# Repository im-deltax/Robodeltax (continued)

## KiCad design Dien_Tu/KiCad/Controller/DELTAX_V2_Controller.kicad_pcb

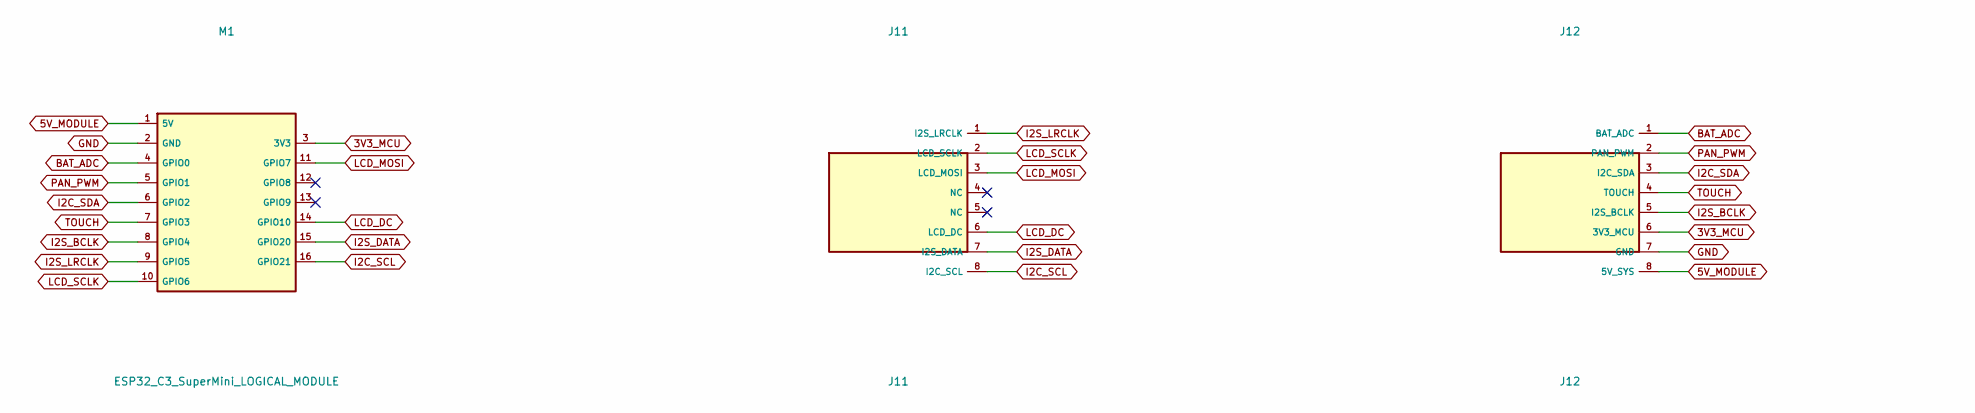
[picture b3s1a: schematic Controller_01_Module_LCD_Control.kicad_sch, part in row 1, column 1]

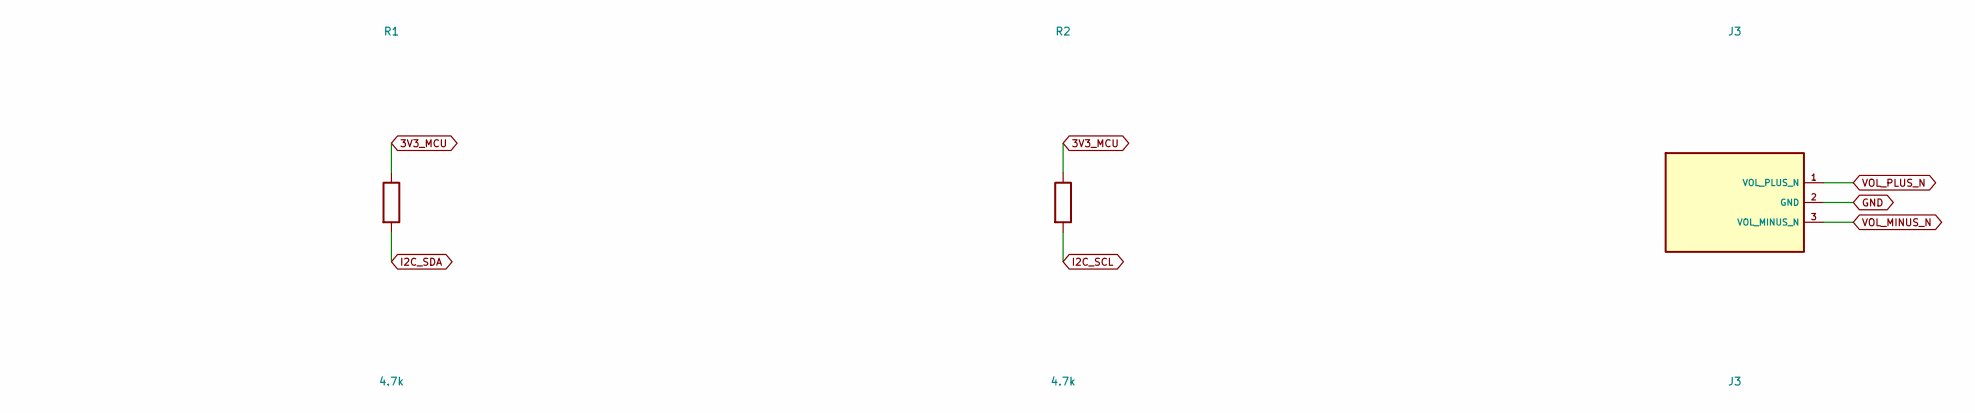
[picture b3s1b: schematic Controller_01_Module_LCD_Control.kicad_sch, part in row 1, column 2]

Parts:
J3: J3; WirePads_3
J11: J11; SLW_108_LowProfile
J12: J12; SLW_108_LowProfile
M1: ESP32_C3_SuperMini_LOGICAL_MODULE
R1, R2: 4.7k; R_0603_1608Metric

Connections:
3V3_MCU: J12.6 (3V3_MCU), M1.3 (3V3), R1.1, R2.1; also elsewhere on the board
5V_MODULE: J12.8 (5V_SYS), M1.1 (5V); also elsewhere on the board
BAT_ADC: J12.1 (BAT_ADC), M1.4 (GPIO0); also elsewhere on the board
GND: J3.2 (GND), J12.7 (GND), M1.2 (GND); also elsewhere on the board
I2C_SCL: J11.8 (I2C_SCL), M1.16 (GPIO21), R2.2; also elsewhere on the board
I2C_SDA: J12.3 (I2C_SDA), M1.6 (GPIO2), R1.2; also elsewhere on the board
I2S_BCLK: J12.5 (I2S_BCLK), M1.8 (GPIO4); also elsewhere on the board
I2S_DATA: J11.7 (I2S_DATA), M1.15 (GPIO20); also elsewhere on the board
I2S_LRCLK: J11.1 (I2S_LRCLK), M1.9 (GPIO5); also elsewhere on the board
LCD_DC: J11.6 (LCD_DC), M1.14 (GPIO10); also elsewhere on the board
LCD_MOSI: J11.3 (LCD_MOSI), M1.11 (GPIO7); also elsewhere on the board
LCD_SCLK: J11.2 (LCD_SCLK), M1.10 (GPIO6); also elsewhere on the board
PAN_PWM: J12.2 (PAN_PWM), M1.5 (GPIO1); also elsewhere on the board
TOUCH: J12.4 (TOUCH), M1.7 (GPIO3); also elsewhere on the board
VOL_MINUS_N: J3.3 (VOL_MINUS_N); also elsewhere on the board
VOL_PLUS_N: J3.1 (VOL_PLUS_N); also elsewhere on the board

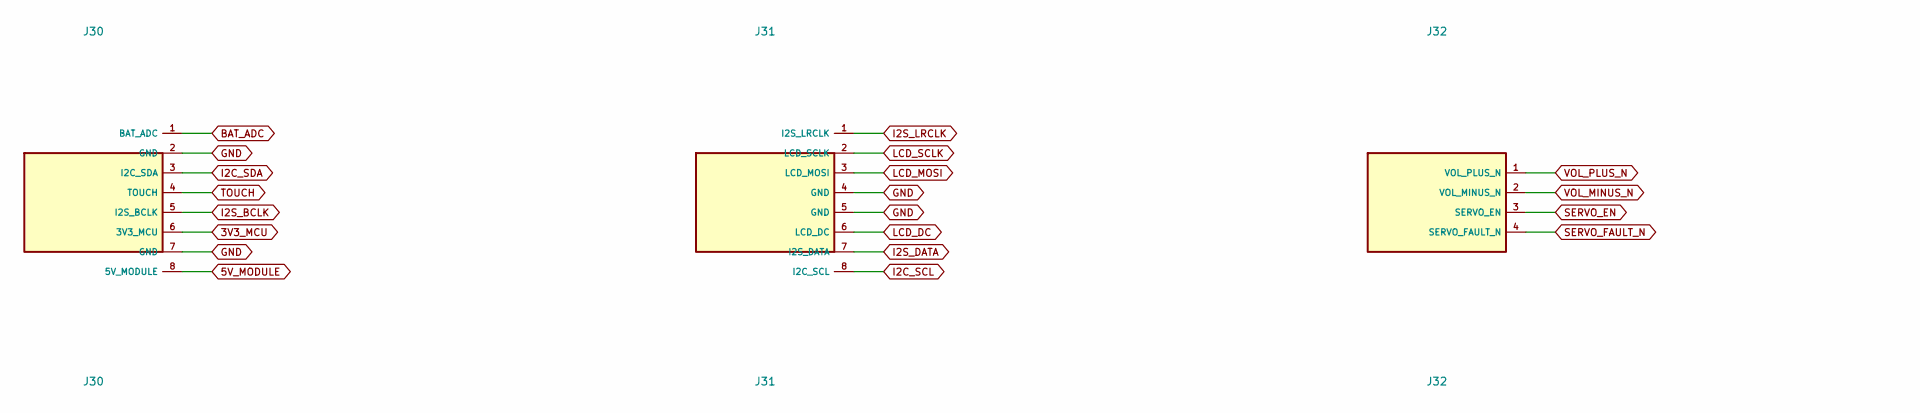
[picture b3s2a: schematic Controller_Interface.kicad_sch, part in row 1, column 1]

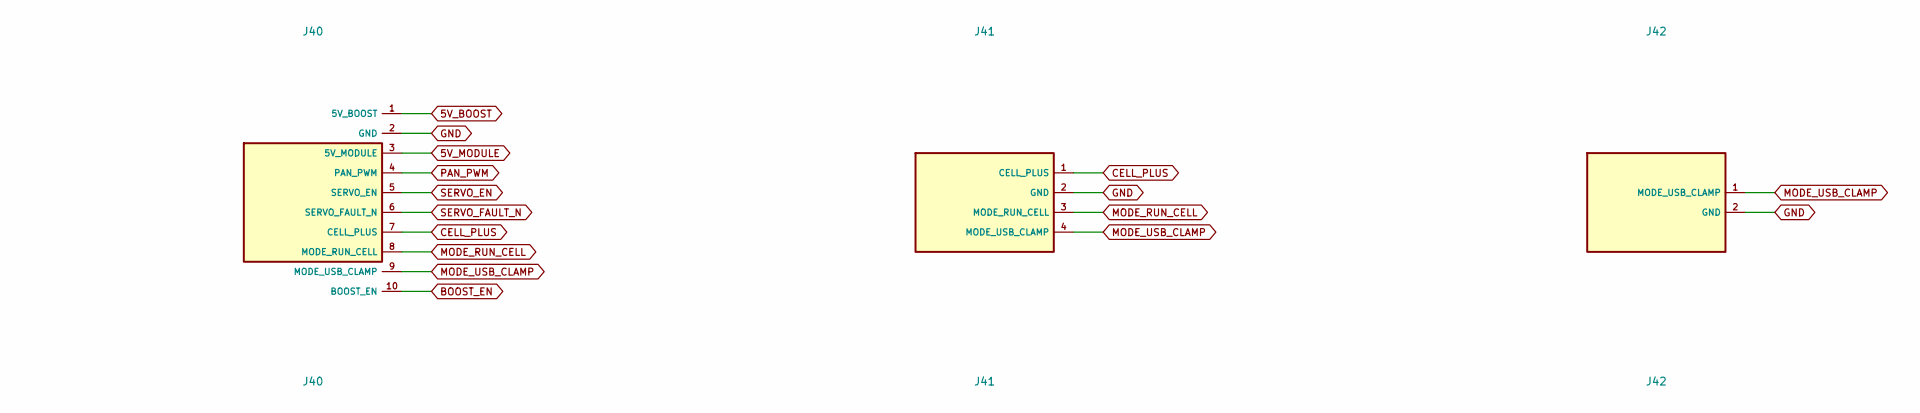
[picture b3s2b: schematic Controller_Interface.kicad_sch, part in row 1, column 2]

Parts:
J30: J30; WirePads_8
J31: J31; WirePads_8
J32: J32; WirePads_4
J40: J40; PowerPads_10
J41: J41; WirePads_4
J42: J42; WirePads_2

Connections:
3V3_MCU: J30.6 (3V3_MCU); also elsewhere on the board
5V_BOOST: J40.1 (5V_BOOST); also elsewhere on the board
5V_MODULE: J30.8 (5V_MODULE), J40.3 (5V_MODULE); also elsewhere on the board
BAT_ADC: J30.1 (BAT_ADC); also elsewhere on the board
BOOST_EN: J40.10 (BOOST_EN); also elsewhere on the board
CELL_PLUS: J40.7 (CELL_PLUS), J41.1 (CELL_PLUS); also elsewhere on the board
GND: J30.2 (GND), J30.7 (GND), J31.4 (GND), J31.5 (GND), J40.2 (GND), J41.2 (GND), J42.2 (GND); also elsewhere on the board
I2C_SCL: J31.8 (I2C_SCL); also elsewhere on the board
I2C_SDA: J30.3 (I2C_SDA); also elsewhere on the board
I2S_BCLK: J30.5 (I2S_BCLK); also elsewhere on the board
I2S_DATA: J31.7 (I2S_DATA); also elsewhere on the board
I2S_LRCLK: J31.1 (I2S_LRCLK); also elsewhere on the board
LCD_DC: J31.6 (LCD_DC); also elsewhere on the board
LCD_MOSI: J31.3 (LCD_MOSI); also elsewhere on the board
LCD_SCLK: J31.2 (LCD_SCLK); also elsewhere on the board
MODE_RUN_CELL: J40.8 (MODE_RUN_CELL), J41.3 (MODE_RUN_CELL); also elsewhere on the board
MODE_USB_CLAMP: J40.9 (MODE_USB_CLAMP), J41.4 (MODE_USB_CLAMP), J42.1 (MODE_USB_CLAMP); also elsewhere on the board
PAN_PWM: J40.4 (PAN_PWM); also elsewhere on the board
SERVO_EN: J32.3 (SERVO_EN), J40.5 (SERVO_EN)
SERVO_FAULT_N: J32.4 (SERVO_FAULT_N), J40.6 (SERVO_FAULT_N)
TOUCH: J30.4 (TOUCH); also elsewhere on the board
VOL_MINUS_N: J32.2 (VOL_MINUS_N); also elsewhere on the board
VOL_PLUS_N: J32.1 (VOL_PLUS_N); also elsewhere on the board

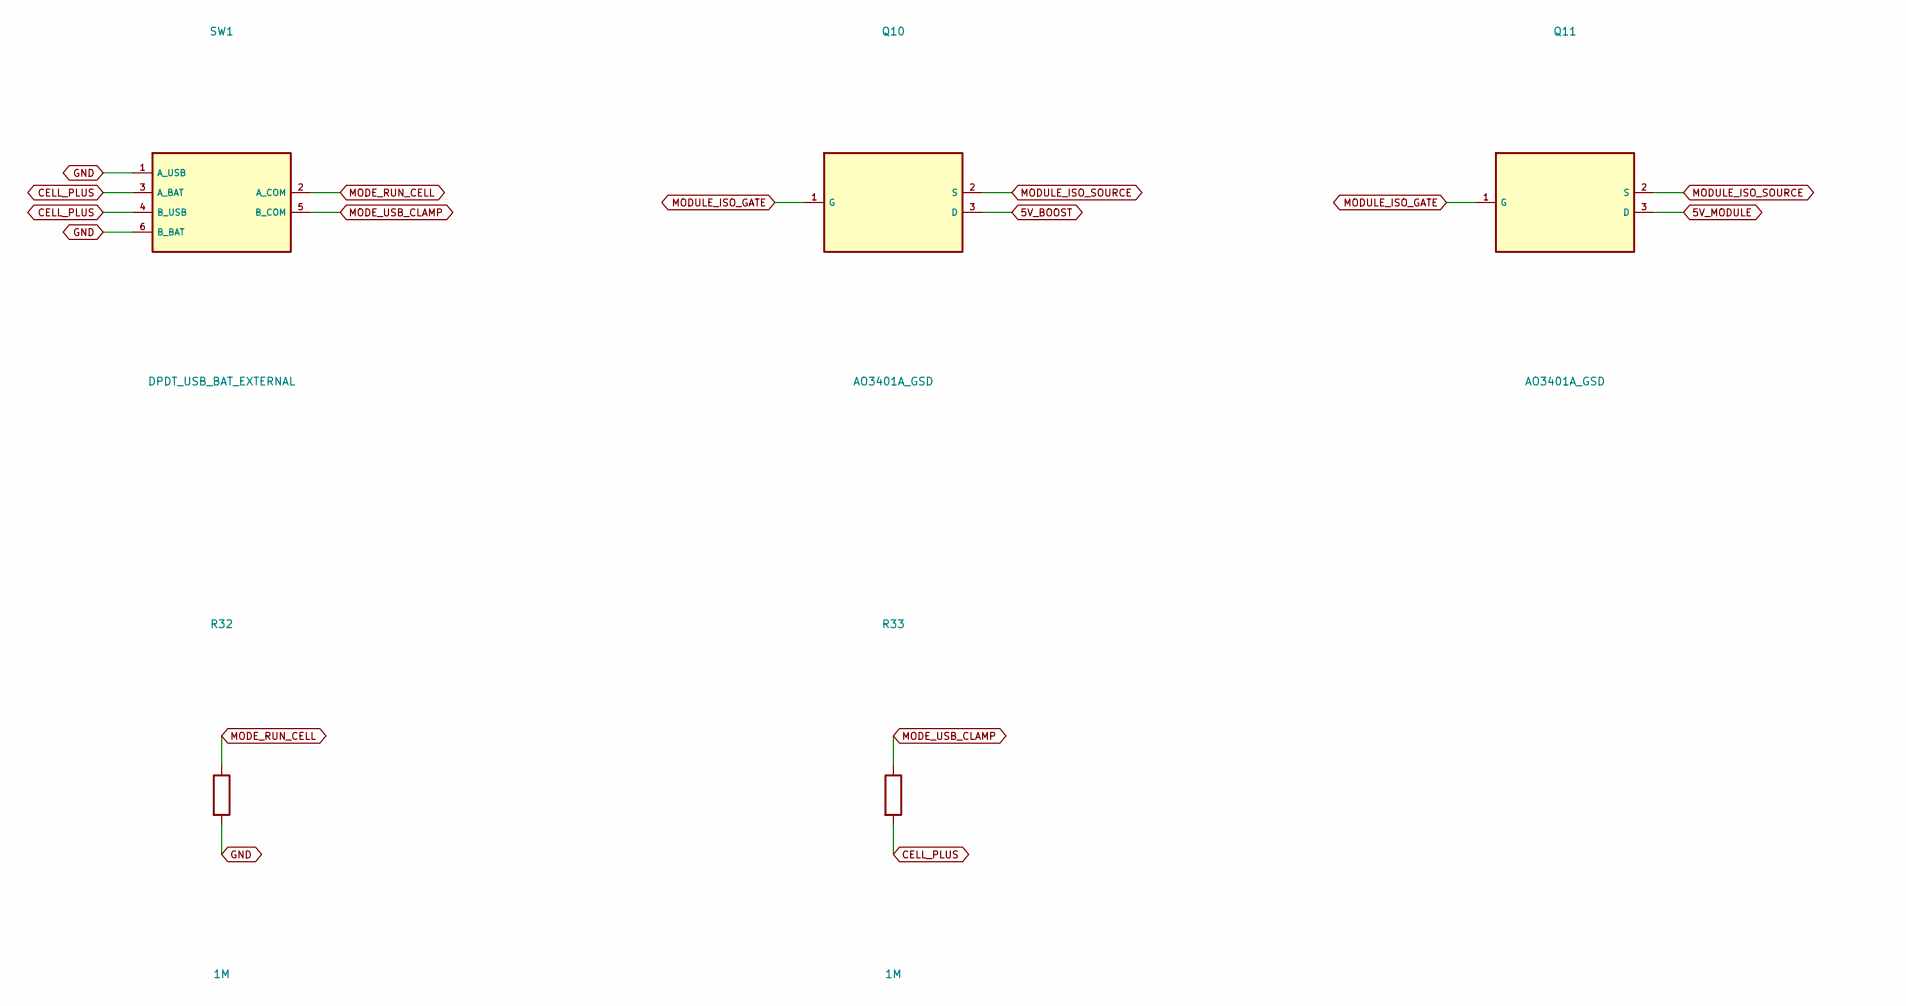
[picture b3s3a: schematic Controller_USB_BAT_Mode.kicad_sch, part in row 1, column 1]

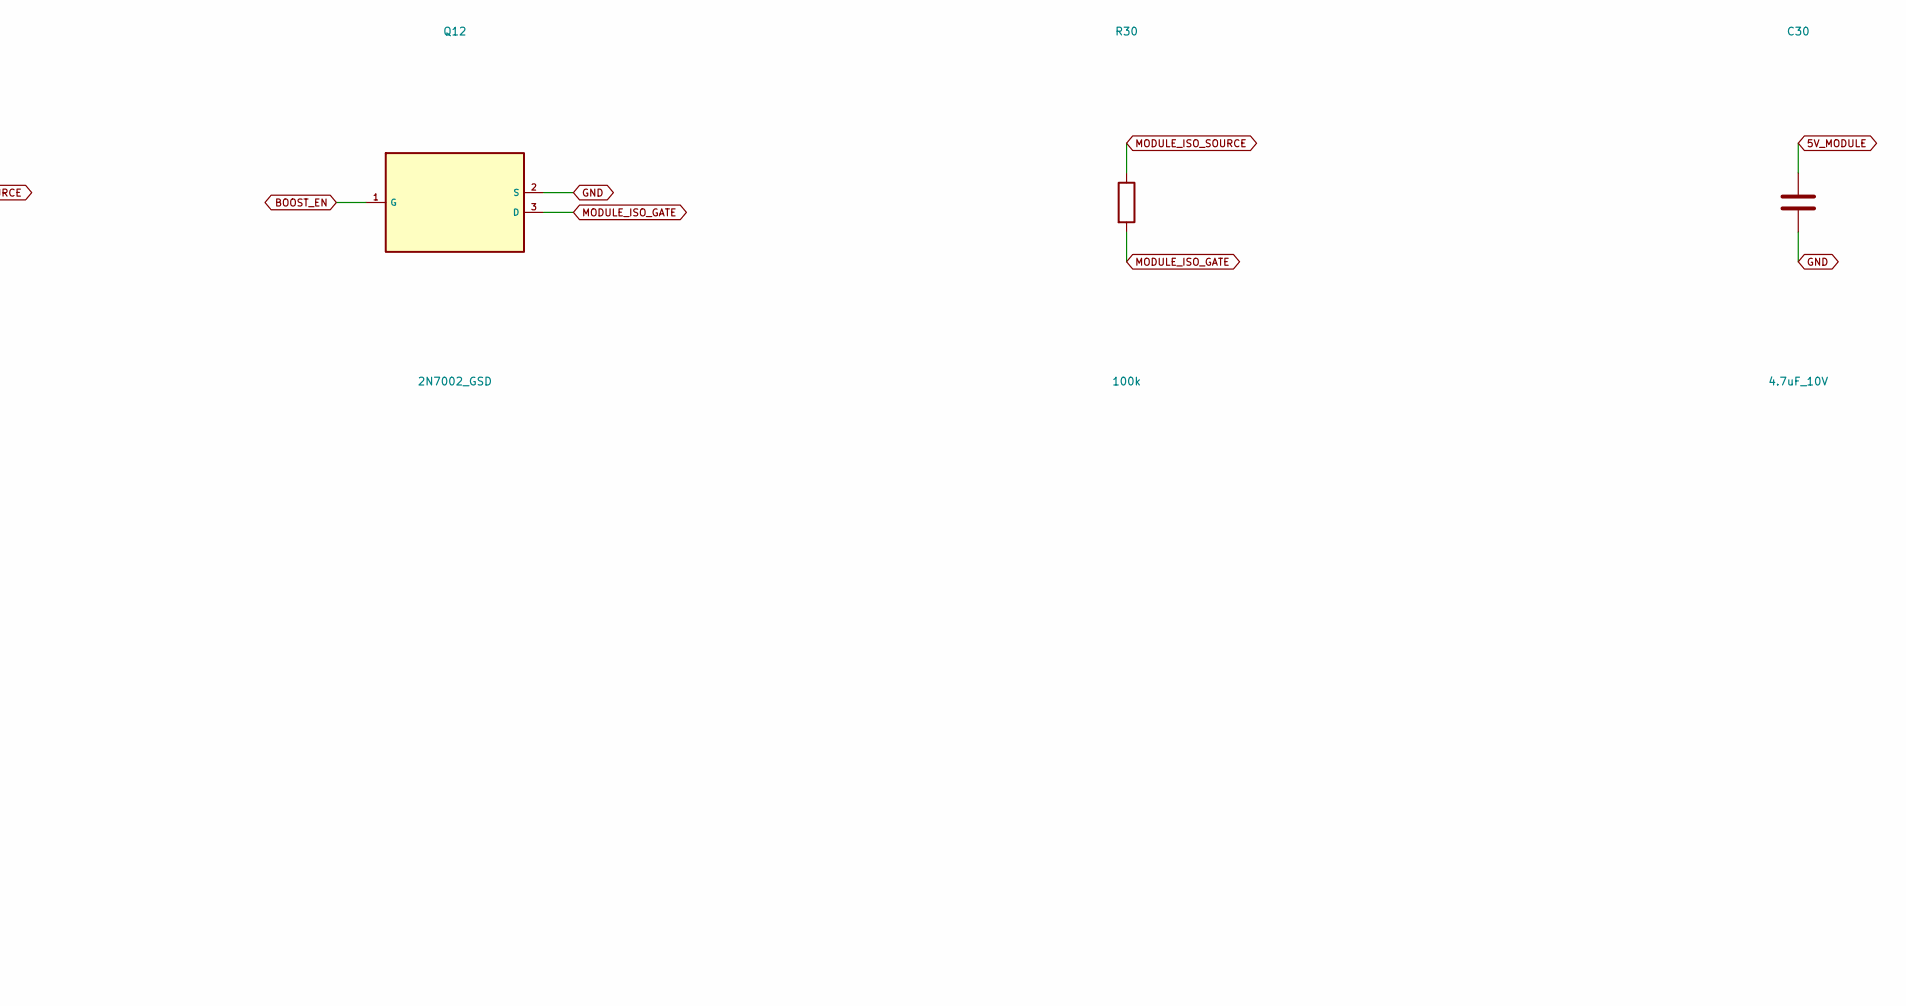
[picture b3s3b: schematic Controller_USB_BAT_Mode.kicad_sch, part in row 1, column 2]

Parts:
C30: 4.7uF_10V; C_0603_1608Metric
Q10, Q11: AO3401A_GSD; SOT-23
Q12: 2N7002_GSD; SOT-23
R30: 100k; R_0603_1608Metric
R32, R33: 1M; R_0603_1608Metric
SW1: DPDT_USB_BAT_EXTERNAL

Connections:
5V_BOOST: Q10.3 (D); also elsewhere on the board
5V_MODULE: C30.1, Q11.3 (D); also elsewhere on the board
BOOST_EN: Q12.1 (G); also elsewhere on the board
CELL_PLUS: R33.2, SW1.3 (A_BAT), SW1.4 (B_USB); also elsewhere on the board
GND: C30.2, Q12.2 (S), R32.2, SW1.1 (A_USB), SW1.6 (B_BAT); also elsewhere on the board
MODE_RUN_CELL: R32.1, SW1.2 (A_COM); also elsewhere on the board
MODE_USB_CLAMP: R33.1, SW1.5 (B_COM); also elsewhere on the board
MODULE_ISO_GATE: Q10.1 (G), Q11.1 (G), Q12.3 (D), R30.2
MODULE_ISO_SOURCE: Q10.2 (S), Q11.2 (S), R30.1

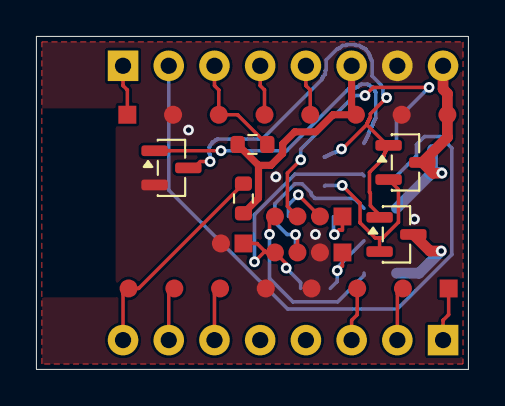
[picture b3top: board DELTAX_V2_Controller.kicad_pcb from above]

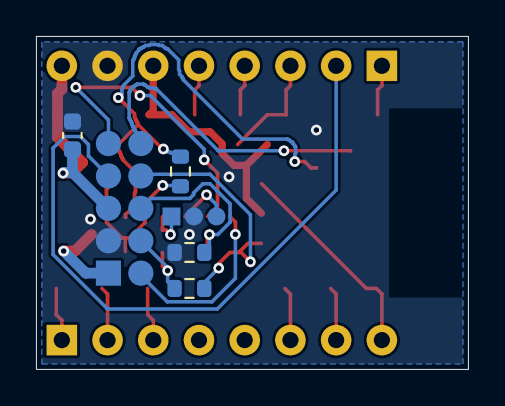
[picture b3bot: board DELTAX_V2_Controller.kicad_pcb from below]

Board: 2 copper layers, 24.0 x 18.5 mm, 18 parts (6 on the bottom side), 25 nets.

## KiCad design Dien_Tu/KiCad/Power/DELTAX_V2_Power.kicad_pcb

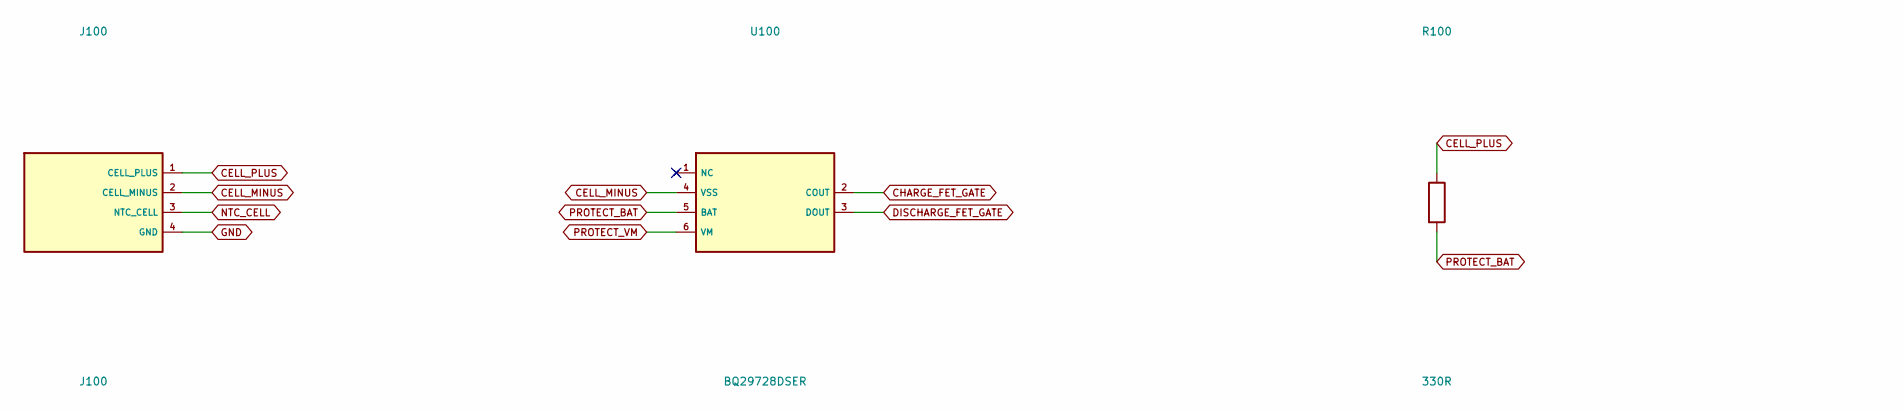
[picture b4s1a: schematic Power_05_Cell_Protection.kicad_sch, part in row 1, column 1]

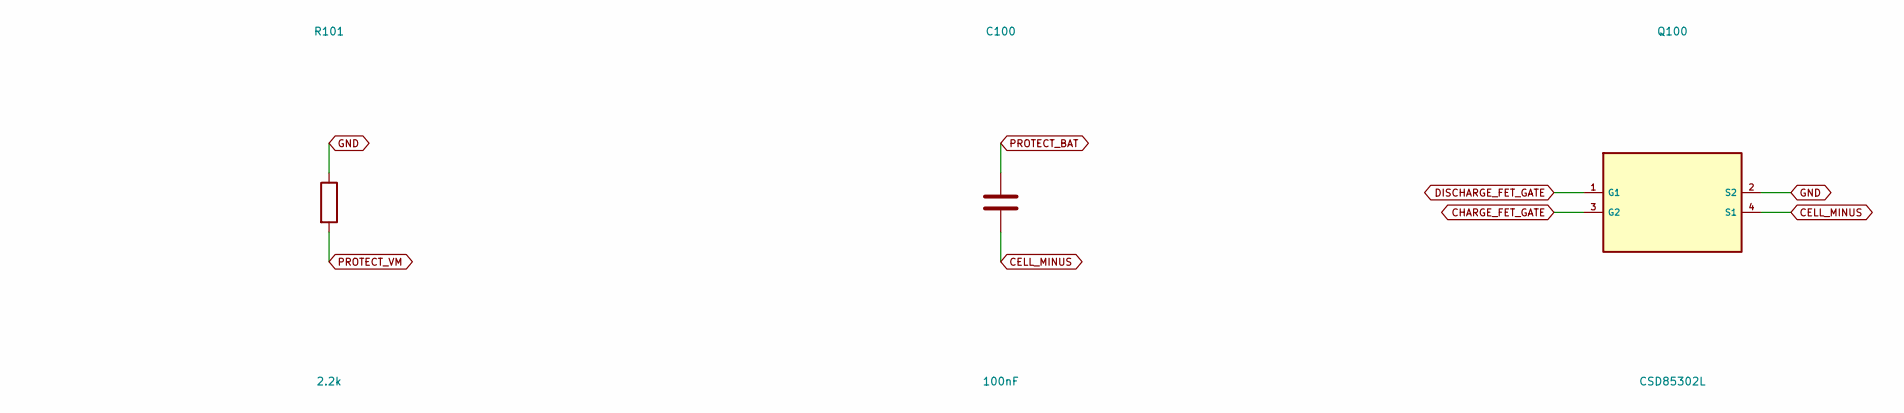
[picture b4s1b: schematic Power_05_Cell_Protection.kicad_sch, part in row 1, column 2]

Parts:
C100: 100nF; C_0603_1608Metric
J100: J100; PowerPads_4
Q100: CSD85302L
R100: 330R; R_0603_1608Metric
R101: 2.2k; R_0603_1608Metric
U100: BQ29728DSER; WSON-6_1.5x1.5mm_P0.5mm

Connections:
CELL_MINUS: C100.2, J100.2 (CELL_MINUS), Q100.4 (S1), U100.4 (VSS)
CELL_PLUS: J100.1 (CELL_PLUS), R100.1; also elsewhere on the board
CHARGE_FET_GATE: Q100.3 (G2), U100.2 (COUT)
DISCHARGE_FET_GATE: Q100.1 (G1), U100.3 (DOUT)
GND: J100.4 (GND), Q100.2 (S2), R101.1; also elsewhere on the board
NTC_CELL: J100.3 (NTC_CELL); also elsewhere on the board
PROTECT_BAT: C100.1, R100.2, U100.5 (BAT)
PROTECT_VM: R101.2, U100.6 (VM)

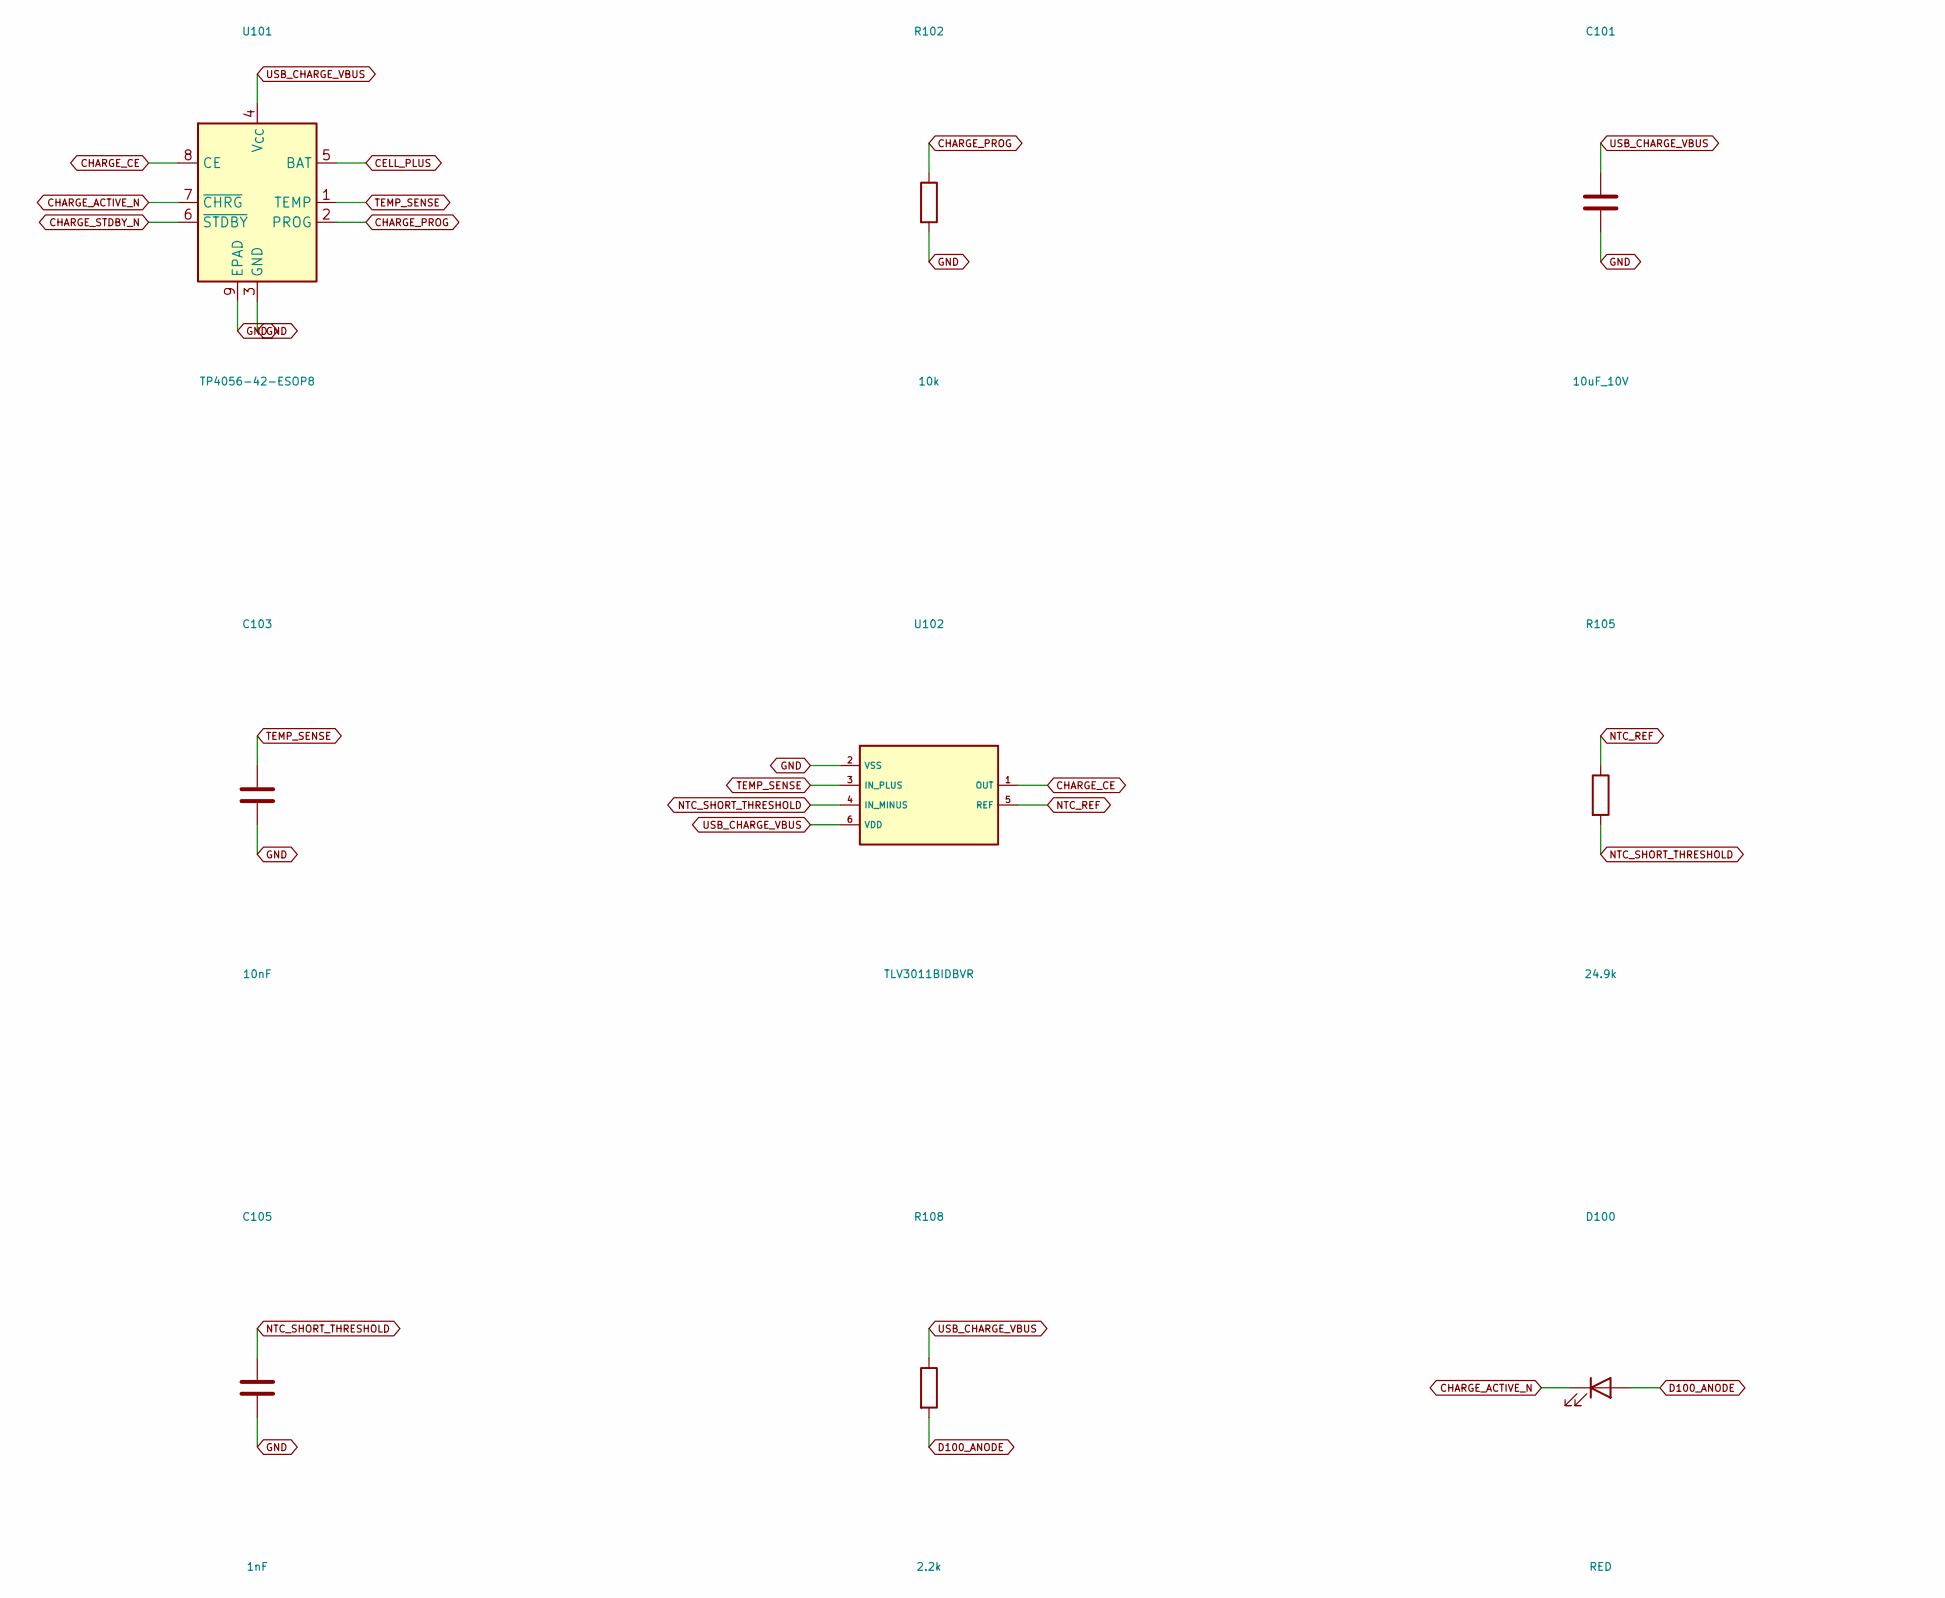
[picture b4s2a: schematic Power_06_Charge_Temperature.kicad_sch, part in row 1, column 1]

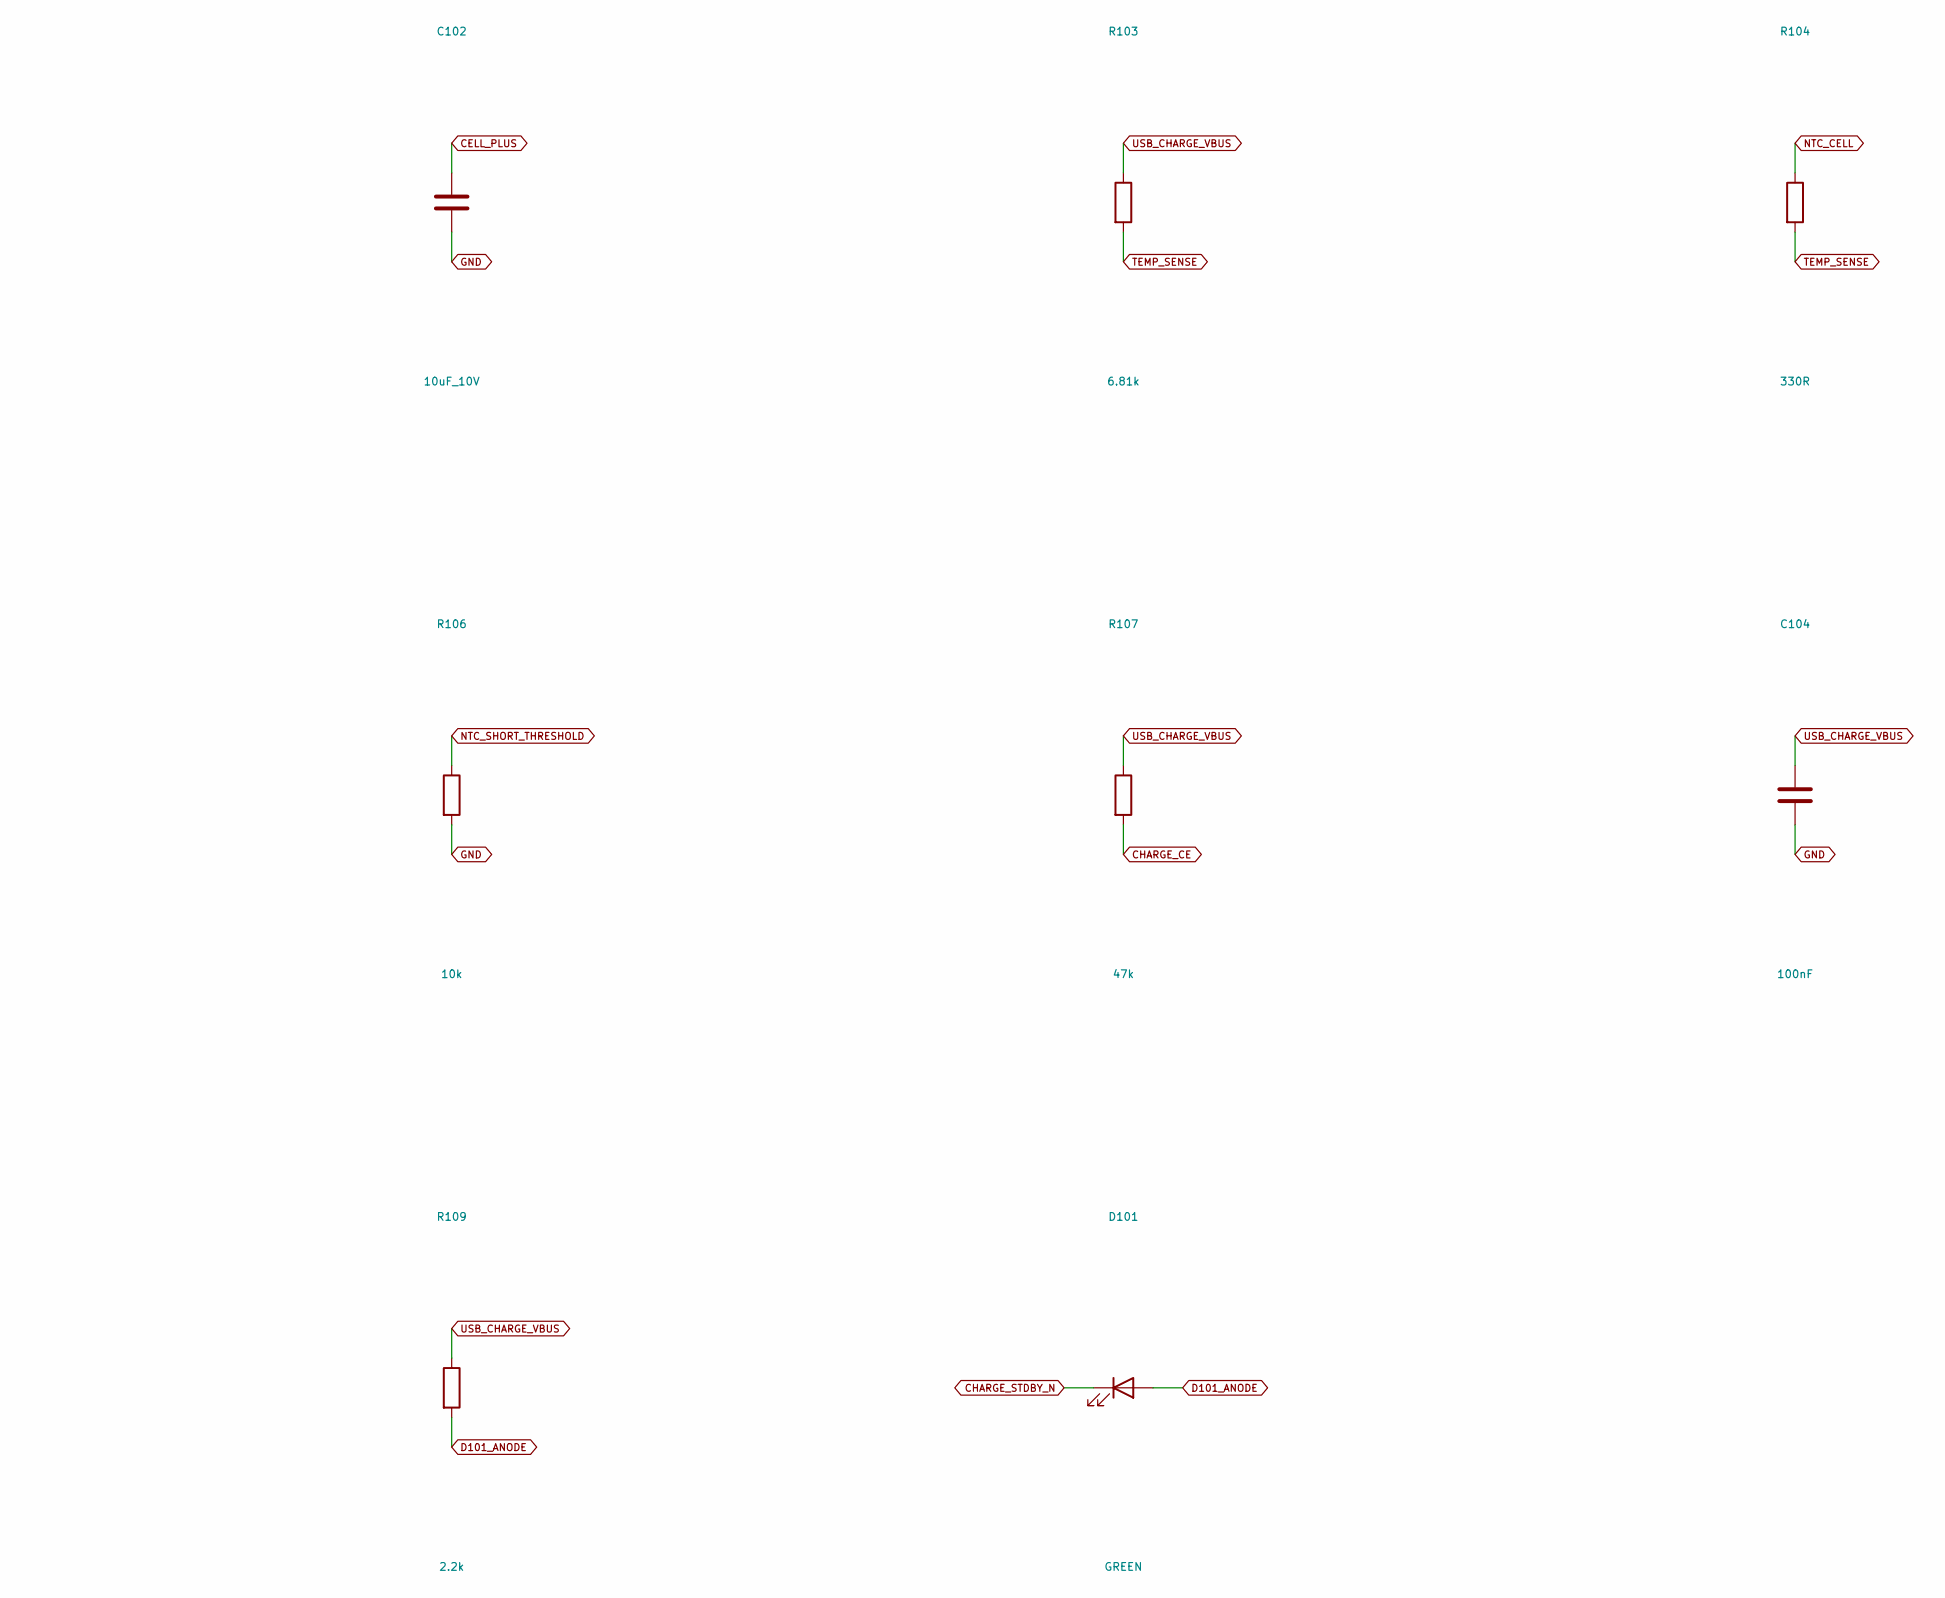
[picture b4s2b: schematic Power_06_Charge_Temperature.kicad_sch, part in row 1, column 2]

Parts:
C101, C102: 10uF_10V; C_0805_2012Metric
C103: 10nF; C_0603_1608Metric
C104: 100nF; C_0603_1608Metric
C105: 1nF; C_0603_1608Metric
D100: RED; LED_0603_1608Metric
D101: GREEN; LED_0603_1608Metric
R102, R106: 10k; R_0603_1608Metric
R103: 6.81k; R_0603_1608Metric
R104: 330R; R_0603_1608Metric
R105: 24.9k; R_0603_1608Metric
R107: 47k; R_0603_1608Metric
R108, R109: 2.2k; R_0603_1608Metric
U101: TP4056-42-ESOP8; SOIC-8-1EP_3.9x4.9mm_P1.27mm_EP2.41x3.3mm
U102: TLV3011BIDBVR; SOT-23-6

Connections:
CELL_PLUS: C102.1, U101.5 (BAT); also elsewhere on the board
CHARGE_ACTIVE_N: D100.1 (K), U101.7 (~CHRG)
CHARGE_CE: R107.2, U101.8 (CE), U102.1 (OUT)
CHARGE_PROG: R102.1, U101.2 (PROG)
CHARGE_STDBY_N: D101.1 (K), U101.6 (~STDBY)
D100_ANODE: D100.2 (A), R108.2
D101_ANODE: D101.2 (A), R109.2
GND: C101.2, C102.2, C103.2, C104.2, C105.2, R102.2, R106.2, U101.3 (GND), U101.9 (EPAD), U102.2 (VSS); also elsewhere on the board
NTC_CELL: R104.1; also elsewhere on the board
NTC_REF: R105.1, U102.5 (REF)
NTC_SHORT_THRESHOLD: C105.1, R105.2, R106.1, U102.4 (IN_MINUS)
TEMP_SENSE: C103.1, R103.2, R104.2, U101.1 (TEMP), U102.3 (IN_PLUS)
USB_CHARGE_VBUS: C101.1, C104.1, R103.1, R107.1, R108.1, R109.1, U101.4 (V_{CC}), U102.6 (VDD); also elsewhere on the board
